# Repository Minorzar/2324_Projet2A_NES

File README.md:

# FPGA NES - Student Project

This repository contains a recreation of the NES console (EU edition) in **VHDL language**. We used **Quartus** for all of the VHDL part of the project, and uploaded it on the **DE1-SoC board RevC (Cyclone V)**. 
Also, this project have a PCB designed for the FPGA board to be able to connect with the NES cartridge. (Realised under KiCad 7.0+). 

## Notes : 6502 CPU

A part of this project replicates the 6502 CPU in VHDL language. Feel free to use whatever part of the code for your projects. 
> **Note:** We aim to create a repository which contains only the 6502. A link will be added to this repository when it will be done.

## Repository Structure

- **Hardware** : The PCB for the Cartridge adaptator. Use the V5 currently. Only the latest version of it will be available later. You still need to buy the cartridge lector himself online, because the PCB only replicate a part of the PCB of the NES.
- **Software** :  Contains the architecture in VHDL of the NES. Details later on the readme.
- **Datasheet** : Contains all the datasheets used for the project. All other data comes from the [NESdev wiki](https://www.nesdev.org/wiki/Nesdev_Wiki).

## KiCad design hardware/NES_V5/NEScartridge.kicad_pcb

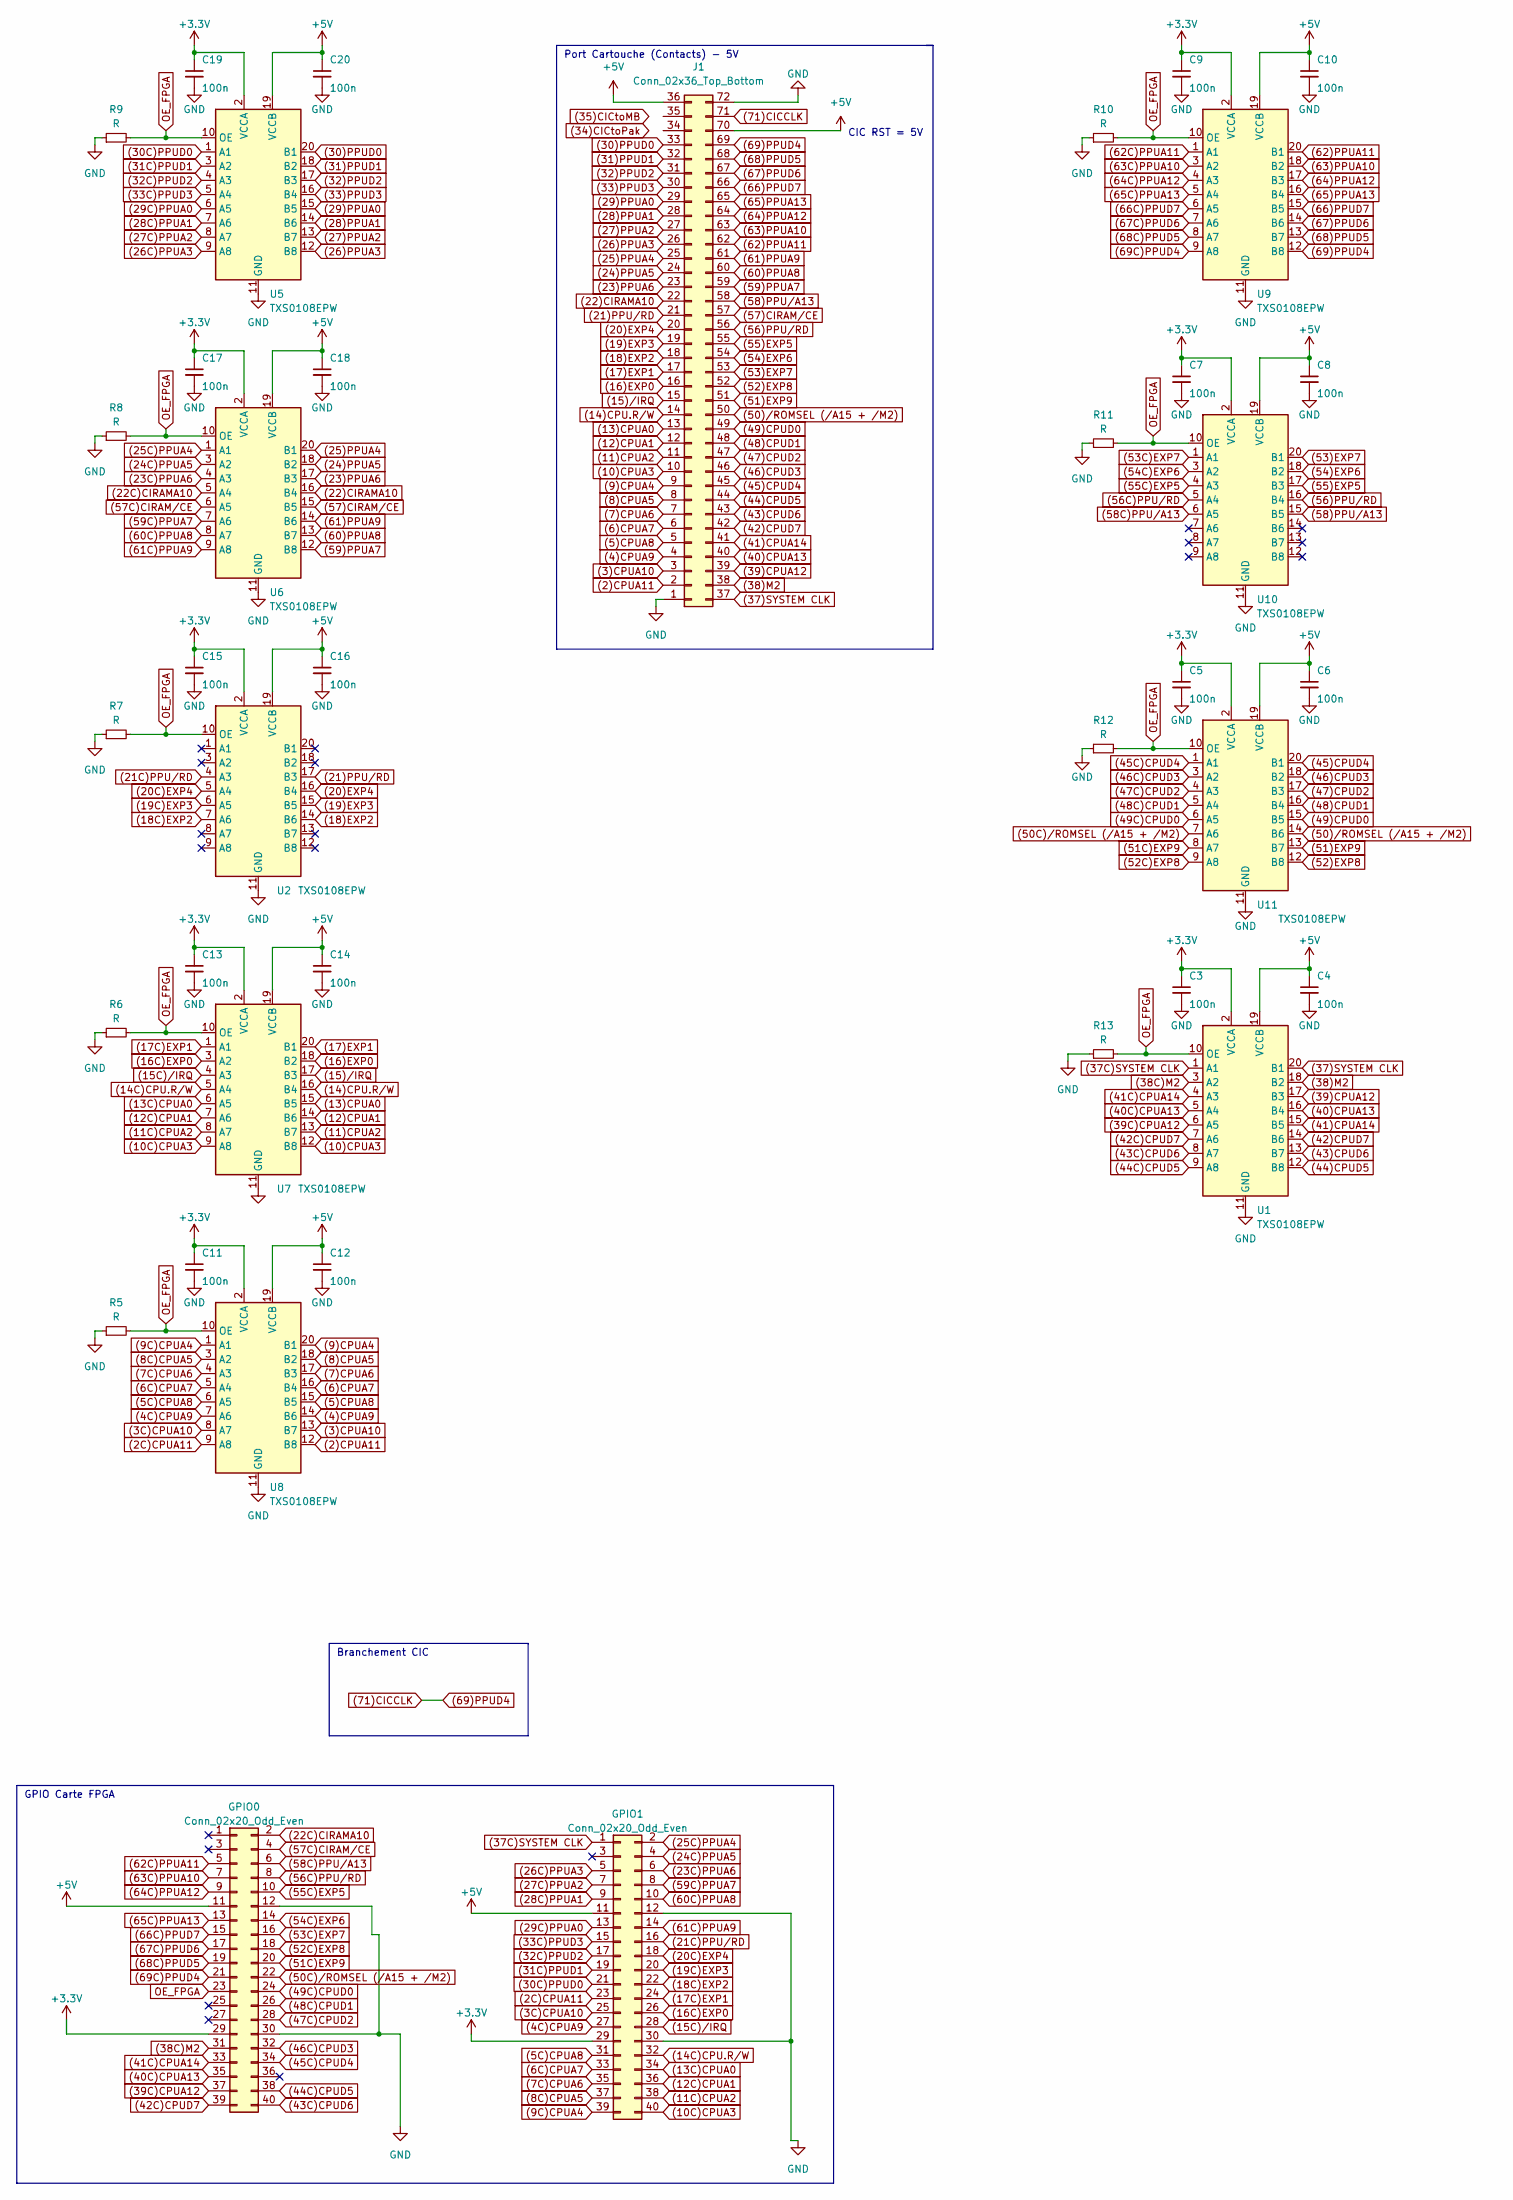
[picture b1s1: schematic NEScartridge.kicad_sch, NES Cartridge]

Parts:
C3, C4, C5, C6, C7, C8, C9, C10, C11, C12, C13, C14, C15, C16, C17, C18, C19, C20: 100n; C_0402_1005Metric
GPIO0, GPIO1: Conn_02x20_Odd_Even; PinHeader_2x20_P2.54mm_Vertical
J1: Conn_02x36_Top_Bottom; NES_Edge_Connector
R5, R6, R7, R8, R9, R10, R11, R12, R13: R; R_0402_1005Metric_Pad0.72x0.64mm_HandSolder
U1, U2, U5, U6, U7, U8, U9, U10, U11: TXS0108EPW; TSSOP-20_4.4x6.5mm_P0.65mm

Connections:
(2)CPUA11: J1.2, U8.12 (B8)
(2C)CPUA11: GPIO1.23, U8.9 (A8)
(3)CPUA10: J1.3, U8.13 (B7)
(3C)CPUA10: GPIO1.25, U8.8 (A7)
(4)CPUA9: J1.4, U8.14 (B6)
(4C)CPUA9: GPIO1.27, U8.7 (A6)
(5)CPUA8: J1.5, U8.15 (B5)
(5C)CPUA8: GPIO1.31, U8.6 (A5)
(6)CPUA7: J1.6, U8.16 (B4)
(6C)CPUA7: GPIO1.33, U8.5 (A4)
(7)CPUA6: J1.7, U8.17 (B3)
(7C)CPUA6: GPIO1.35, U8.4 (A3)
(8)CPUA5: J1.8, U8.18 (B2)
(8C)CPUA5: GPIO1.37, U8.3 (A2)
(9)CPUA4: J1.9, U8.20 (B1)
(9C)CPUA4: GPIO1.39, U8.1 (A1)
(10)CPUA3: J1.10, U7.12 (B8)
(10C)CPUA3: GPIO1.40, U7.9 (A8)
(11)CPUA2: J1.11, U7.13 (B7)
(11C)CPUA2: GPIO1.38, U7.8 (A7)
(12)CPUA1: J1.12, U7.14 (B6)
(12C)CPUA1: GPIO1.36, U7.7 (A6)
(13)CPUA0: J1.13, U7.15 (B5)
(13C)CPUA0: GPIO1.34, U7.6 (A5)
(14)CPU.R/W: J1.14, U7.16 (B4)
(14C)CPU.R/W: GPIO1.32, U7.5 (A4)
(15)/IRQ: J1.15, U7.17 (B3)
(15C)/IRQ: GPIO1.28, U7.4 (A3)
(16)EXP0: J1.16, U7.18 (B2)
(16C)EXP0: GPIO1.26, U7.3 (A2)
(17)EXP1: J1.17, U7.20 (B1)
(17C)EXP1: GPIO1.24, U7.1 (A1)
(18)EXP2: J1.18, U2.14 (B6)
(18C)EXP2: GPIO1.22, U2.7 (A6)
(19)EXP3: J1.19, U2.15 (B5)
(19C)EXP3: GPIO1.20, U2.6 (A5)
(20)EXP4: J1.20, U2.16 (B4)
(20C)EXP4: GPIO1.18, U2.5 (A4)
(21)PPU/RD: J1.21, U2.17 (B3)
(21C)PPU/RD: GPIO1.16, U2.4 (A3)
(22)CIRAMA10: J1.22, U6.16 (B4)
(22C)CIRAMA10: GPIO0.2, U6.5 (A4)
(23)PPUA6: J1.23, U6.17 (B3)
(23C)PPUA6: GPIO1.6, U6.4 (A3)
(24)PPUA5: J1.24, U6.18 (B2)
(24C)PPUA5: GPIO1.4, U6.3 (A2)
(25)PPUA4: J1.25, U6.20 (B1)
(25C)PPUA4: GPIO1.2, U6.1 (A1)
(26)PPUA3: J1.26, U5.12 (B8)
(26C)PPUA3: GPIO1.5, U5.9 (A8)
(27)PPUA2: J1.27, U5.13 (B7)
(27C)PPUA2: GPIO1.7, U5.8 (A7)
(28)PPUA1: J1.28, U5.14 (B6)
(28C)PPUA1: GPIO1.9, U5.7 (A6)
(29)PPUA0: J1.29, U5.15 (B5)
(29C)PPUA0: GPIO1.13, U5.6 (A5)
(30)PPUD0: J1.33, U5.20 (B1)
(30C)PPUD0: GPIO1.21, U5.1 (A1)
(31)PPUD1: J1.32, U5.18 (B2)
(31C)PPUD1: GPIO1.19, U5.3 (A2)
(32)PPUD2: J1.31, U5.17 (B3)
(32C)PPUD2: GPIO1.17, U5.4 (A3)
(33)PPUD3: J1.30, U5.16 (B4)
(33C)PPUD3: GPIO1.15, U5.5 (A4)
(34)CICtoPak: J1.34
(35)CICtoMB: J1.35
(37)SYSTEM CLK: J1.37, U1.20 (B1)
(37C)SYSTEM CLK: GPIO1.1, U1.1 (A1)
(38)M2: J1.38, U1.18 (B2)
(38C)M2: GPIO0.31, U1.3 (A2)
(39)CPUA12: J1.39, U1.17 (B3)
(39C)CPUA12: GPIO0.37, U1.6 (A5)
(40)CPUA13: J1.40, U1.16 (B4)
(40C)CPUA13: GPIO0.35, U1.5 (A4)
(41)CPUA14: J1.41, U1.15 (B5)
(41C)CPUA14: GPIO0.33, U1.4 (A3)
(42)CPUD7: J1.42, U1.14 (B6)
(42C)CPUD7: GPIO0.39, U1.7 (A6)
(43)CPUD6: J1.43, U1.13 (B7)
(43C)CPUD6: GPIO0.40, U1.8 (A7)
(44)CPUD5: J1.44, U1.12 (B8)
(44C)CPUD5: GPIO0.38, U1.9 (A8)
(45)CPUD4: J1.45, U11.20 (B1)
(45C)CPUD4: GPIO0.34, U11.1 (A1)
(46)CPUD3: J1.46, U11.18 (B2)
(46C)CPUD3: GPIO0.32, U11.3 (A2)
(47)CPUD2: J1.47, U11.17 (B3)
(47C)CPUD2: GPIO0.28, U11.4 (A3)
(48)CPUD1: J1.48, U11.16 (B4)
(48C)CPUD1: GPIO0.26, U11.5 (A4)
(49)CPUD0: J1.49, U11.15 (B5)
(49C)CPUD0: GPIO0.24, U11.6 (A5)
(50)/ROMSEL (/A15 + /M2): J1.50, U11.14 (B6)
(50C)/ROMSEL (/A15 + /M2): GPIO0.22, U11.7 (A6)
(51)EXP9: J1.51, U11.13 (B7)
(51C)EXP9: GPIO0.20, U11.8 (A7)
(52)EXP8: J1.52, U11.12 (B8)
(52C)EXP8: GPIO0.18, U11.9 (A8)
(53)EXP7: J1.53, U10.20 (B1)
(53C)EXP7: GPIO0.16, U10.1 (A1)
(54)EXP6: J1.54, U10.18 (B2)
(54C)EXP6: GPIO0.14, U10.3 (A2)
(55)EXP5: J1.55, U10.17 (B3)
(55C)EXP5: GPIO0.10, U10.4 (A3)
(56)PPU/RD: J1.56, U10.16 (B4)
(56C)PPU/RD: GPIO0.8, U10.5 (A4)
(57)CIRAM/CE: J1.57, U6.15 (B5)
(57C)CIRAM/CE: GPIO0.4, U6.6 (A5)
(58)PPU/A13: J1.58, U10.15 (B5)
(58C)PPU/A13: GPIO0.6, U10.6 (A5)
(59)PPUA7: J1.59, U6.12 (B8)
(59C)PPUA7: GPIO1.8, U6.7 (A6)
(60)PPUA8: J1.60, U6.13 (B7)
(60C)PPUA8: GPIO1.10, U6.8 (A7)
(61)PPUA9: J1.61, U6.14 (B6)
(61C)PPUA9: GPIO1.14, U6.9 (A8)
(62)PPUA11: J1.62, U9.20 (B1)
(62C)PPUA11: GPIO0.5, U9.1 (A1)
(63)PPUA10: J1.63, U9.18 (B2)
(63C)PPUA10: GPIO0.7, U9.3 (A2)
(64)PPUA12: J1.64, U9.17 (B3)
(64C)PPUA12: GPIO0.9, U9.4 (A3)
(65)PPUA13: J1.65, U9.16 (B4)
(65C)PPUA13: GPIO0.13, U9.5 (A4)
(66)PPUD7: J1.66, U9.15 (B5)
(66C)PPUD7: GPIO0.15, U9.6 (A5)
(67)PPUD6: J1.67, U9.14 (B6)
(67C)PPUD6: GPIO0.17, U9.7 (A6)
(68)PPUD5: J1.68, U9.13 (B7)
(68C)PPUD5: GPIO0.19, U9.8 (A7)
(69)PPUD4: J1.69, J1.71, U9.12 (B8)
(69C)PPUD4: GPIO0.21, U9.9 (A8)
+3.3V: C3.1, C5.1, C7.1, C9.1, C11.1, C13.1, C15.1, C17.1, C19.1, GPIO0.29, GPIO1.29, U1.2 (VCCA), U2.2 (VCCA), U5.2 (VCCA), U6.2 (VCCA), U7.2 (VCCA), U8.2 (VCCA), U9.2 (VCCA), U10.2 (VCCA), U11.2 (VCCA)
+5V: C4.1, C6.1, C8.1, C10.1, C12.1, C14.1, C16.1, C18.1, C20.1, GPIO0.11, GPIO1.11, J1.36, J1.70, U1.19 (VCCB), U2.19 (VCCB), U5.19 (VCCB), U6.19 (VCCB), U7.19 (VCCB), U8.19 (VCCB), U9.19 (VCCB), U10.19 (VCCB), U11.19 (VCCB)
GND: C3.2, C4.2, C5.2, C6.2, C7.2, C8.2, C9.2, C10.2, C11.2, C12.2, C13.2, C14.2, C15.2, C16.2, C17.2, C18.2, C19.2, C20.2, GPIO0.12, GPIO0.30, GPIO1.12, GPIO1.30, J1.1, J1.72, R5.1, R6.1, R7.1, R8.1, R9.1, R10.1, R11.1, R12.1, R13.1, U1.11 (GND), U2.11 (GND), U5.11 (GND), U6.11 (GND), U7.11 (GND), U8.11 (GND), U9.11 (GND), U10.11 (GND), U11.11 (GND)
OE_FPGA: GPIO0.23, R5.2, R6.2, R7.2, R8.2, R9.2, R10.2, R11.2, R12.2, R13.2, U1.10 (OE), U2.10 (OE), U5.10 (OE), U6.10 (OE), U7.10 (OE), U8.10 (OE), U9.10 (OE), U10.10 (OE), U11.10 (OE)

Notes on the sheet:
Port Cartouche (Contacts) - 5V
CIC RST = 5V
GPIO Carte FPGA
Branchement CIC

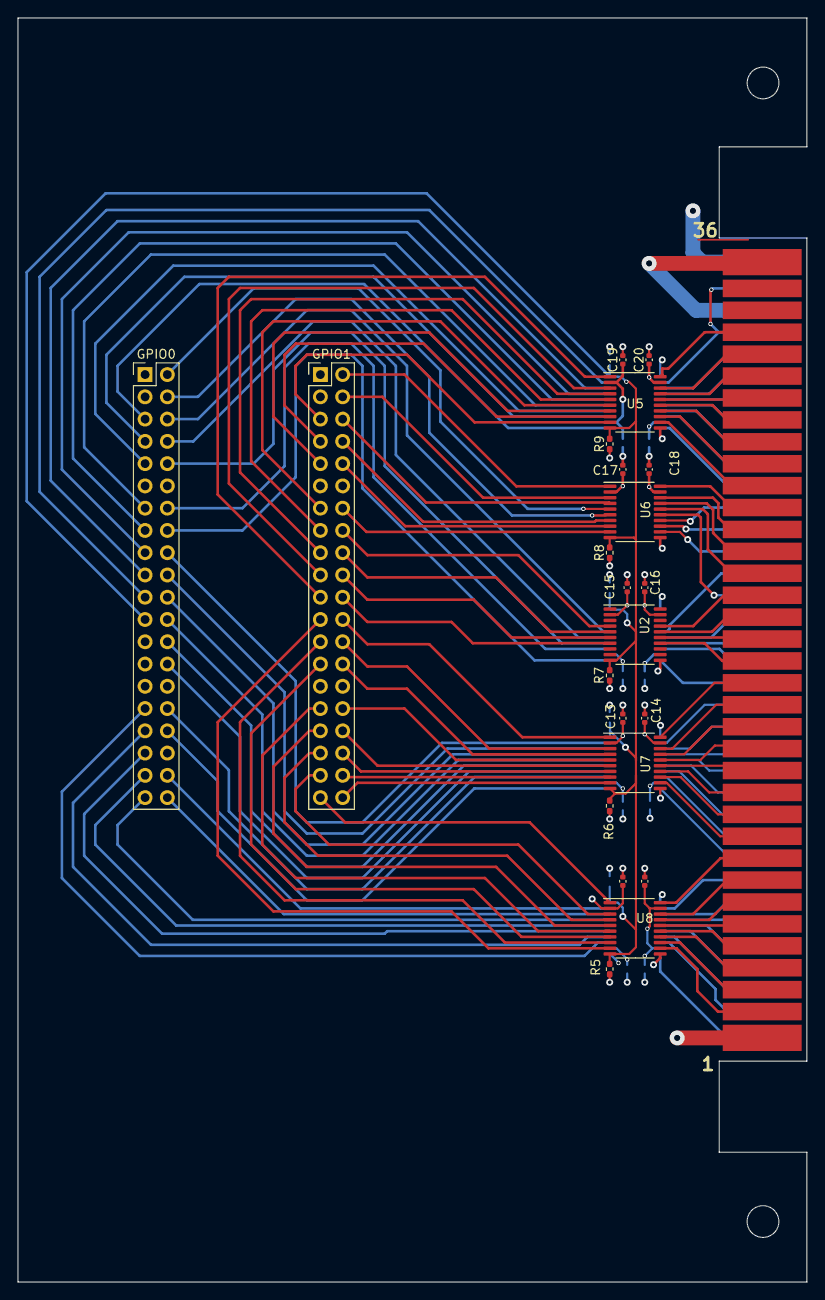
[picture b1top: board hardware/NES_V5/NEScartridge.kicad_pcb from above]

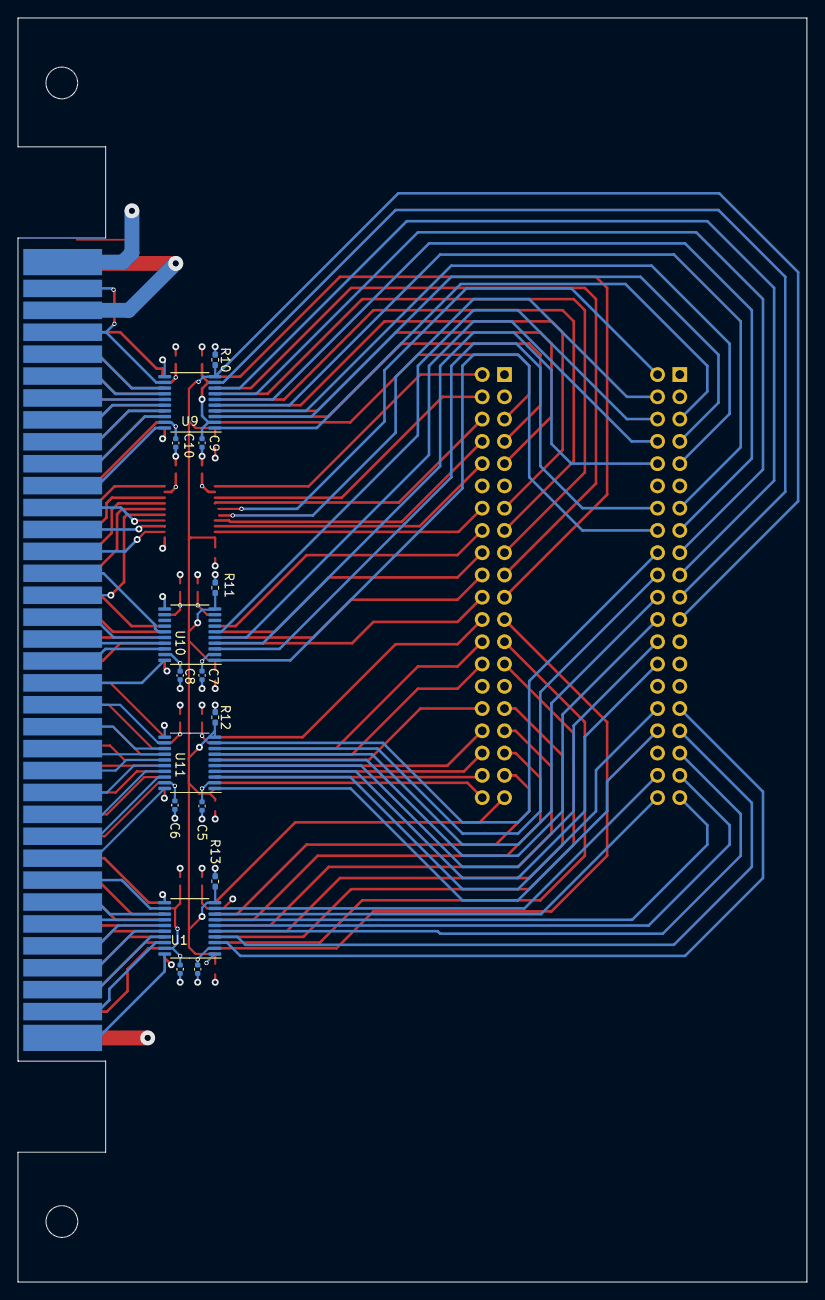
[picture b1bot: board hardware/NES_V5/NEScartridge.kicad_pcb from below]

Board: 4 copper layers, 90.0 x 144.2 mm, 39 parts (16 on the bottom side), 134 nets.

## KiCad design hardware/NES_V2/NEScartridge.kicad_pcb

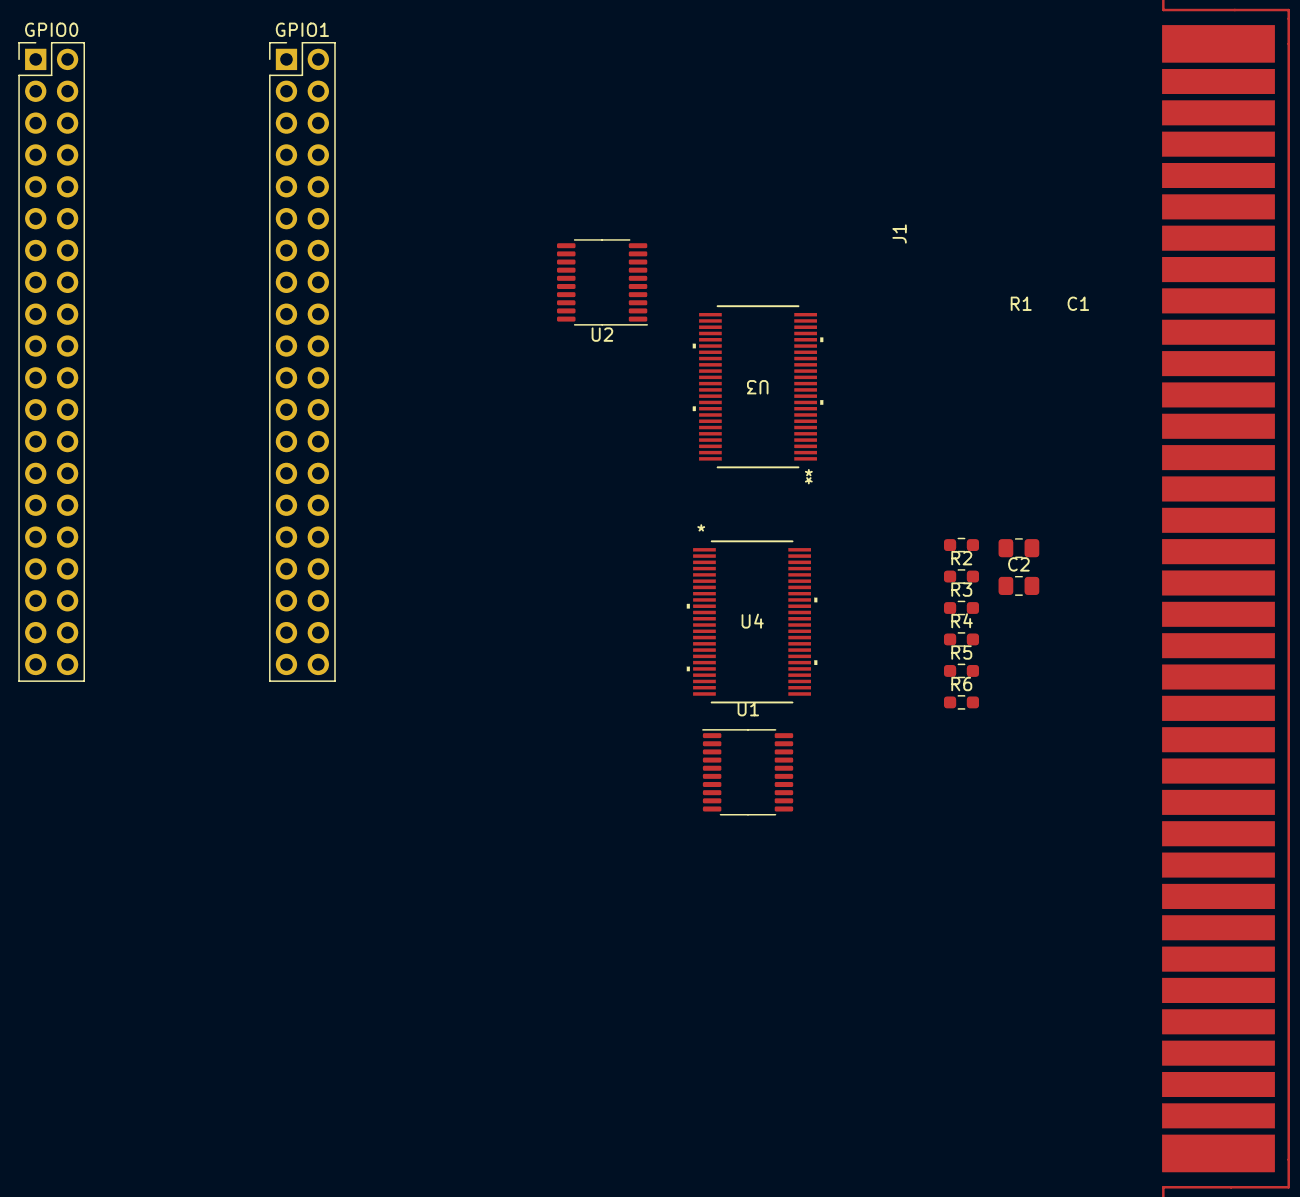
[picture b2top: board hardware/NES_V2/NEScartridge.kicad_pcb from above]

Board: 2 copper layers, 15 parts (0 on the bottom side), 98 nets, no tracks yet.

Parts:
C1, C2: 0.1 uF; C_0805_2012Metric_Pad1.18x1.45mm_HandSolder
GPIO0, GPIO1: Conn_02x20_Odd_Even; PinHeader_2x20_P2.54mm_Vertical
J1: Conn_02x36_Top_Bottom; NES_Edge_Connector
R1, R2: 10k; R_0603_1608Metric_Pad0.98x0.95mm_HandSolder
R3, R4, R5, R6: R; R_0603_1608Metric_Pad0.98x0.95mm_HandSolder
U1, U2: TXS0108EPW; TSSOP-20_4.4x6.5mm_P0.65mm
U3, U4: 74ALVC164245DGG; SOT362-1_NXP-M

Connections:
(2)CPUA11: J1.2, U3.17 (2B3)
(2C)CPUA11: GPIO0.27, U3.32 (2A3)
(3)CPUA10: J1.3, U3.16 (2B2)
(3C)CPUA10: GPIO0.25, U3.33 (2A2)
(4)CPUA9: J1.4, U3.14 (2B1)
(4C)CPUA9: GPIO0.23, U3.35 (2A1)
(5)CPUA8: J1.5, U3.13 (2B0)
(5C)CPUA8: GPIO0.21, U3.36 (2A0)
(6)CPUA7: J1.6, U3.12 (1B7)
(6C)CPUA7: GPIO0.19, U3.37 (1A7)
(7)CPUA6: J1.7, U3.11 (1B6)
(7C)CPUA6: GPIO0.17, U3.38 (1A6)
(8)CPUA5: J1.8, U3.9 (1B5)
(8C)CPUA5: GPIO0.15, U3.40 (1A5)
(9)CPUA4: J1.9, U3.8 (1B4)
(9C)CPUA4: GPIO0.9, U3.41 (1A4)
(10)CPUA3: J1.10, U3.6 (1B3)
(10C)CPUA3: GPIO0.7, U3.43 (1A3)
(11)CPUA2: J1.11, U3.5 (1B2)
(11C)CPUA2: GPIO0.5, U3.44 (1A2)
(12)CPUA1: J1.12, U3.3 (1B1)
(12C)CPUA1: GPIO0.3, U3.46 (1A1)
(13)CPUA0: J1.13, U3.2 (1B0)
(13C)CPUA0: GPIO0.13, U3.47 (1A0)
(23)PPUA6: J1.23, U4.11 (1B6)
(23C)PPUA6: GPIO1.16, U4.38 (1A6)
(24)PPUA5: J1.24, U4.9 (1B5)
(24C)PPUA5: GPIO1.14, U4.40 (1A5)
(25)PPUA4: J1.25, U4.8 (1B4)
(25C)PPUA4: GPIO1.10, U4.41 (1A4)
(26)PPUA3: J1.26, U4.6 (1B3)
(26C)PPUA3: GPIO1.8, U4.43 (1A3)
(27)PPUA2: J1.27, U4.5 (1B2)
(27C)PPUA2: GPIO1.6, U4.44 (1A2)
(28)PPUA1: J1.28, U4.3 (1B1)
(28C)PPUA1: GPIO1.4, U4.46 (1A1)
(29)PPUA0: J1.29, U4.2 (1B0)
(29C)PPUA0: GPIO1.2, U4.47 (1A0)
(30)PPUD0: J1.33, U1.20 (B1)
(30C)PPUD0: GPIO1.9, U1.1 (A1)
(31)PPUD1: J1.32, U1.18 (B2)
(31C)PPUD1: GPIO1.13, U1.3 (A2)
(32)PPUD2: J1.31, U1.17 (B3)
(32C)PPUD2: GPIO1.15, U1.4 (A3)
(33)PPUD3: J1.30, U1.16 (B4)
(33C)PPUD3: GPIO1.17, U1.5 (A4)
(39C)CPUA12: GPIO0.31, U3.19 (2B4), U3.30 (2A4)
(40C)CPUA13: GPIO0.33, U3.20 (2B5), U3.29 (2A5)
(41C)CPUA14: GPIO0.35, U3.22 (2B6), U3.27 (2A6)
(42)CPUD7: J1.42, U2.12 (B8)
(42C)CPUD7: GPIO0.18, U2.9 (A8)
(43)CPUD6: J1.43, U2.13 (B7)
(43C)CPUD6: GPIO0.16, U2.8 (A7)
(44)CPUD5: J1.44, U2.14 (B6)
(44C)CPUD5: GPIO0.14, U2.7 (A6)
(45)CPUD4: J1.45, U2.15 (B5)
(45C)CPUD4: GPIO0.10, U2.6 (A5)
(46)CPUD3: J1.46, U2.16 (B4)
(46C)CPUD3: GPIO0.8, U2.5 (A4)
(47)CPUD2: J1.47, U2.17 (B3)
(47C)CPUD2: GPIO0.6, U2.4 (A3)
(48)CPUD1: J1.48, U2.18 (B2)
(48C)CPUD1: GPIO0.4, U2.3 (A2)
(49)CPUD0: J1.49, U2.20 (B1)
(49C)CPUD0: GPIO0.2, U2.1 (A1)
(59)PPUA7: J1.59, U4.12 (1B7)
(59C)PPUA7: GPIO1.18, U4.37 (1A7)
(60)PPUA8: J1.60, U4.13 (2B0)
(60C)PPUA8: GPIO1.20, U4.36 (2A0)
(61)PPUA9: J1.61, U4.14 (2B1)
(61C)PPUA9: GPIO1.22, U4.35 (2A1)
(62)PPUA11: J1.62, U4.16 (2B2)
(62C)PPUA11: GPIO1.24, U4.33 (2A2)
(63)PPUA10: J1.63, U4.17 (2B3)
(63C)PPUA10: GPIO1.26, U4.32 (2A3)
(64)PPUA12: J1.64, U4.19 (2B4)
(64C)PPUA12: GPIO1.28, U4.30 (2A4)
(65)PPUA13: J1.65, U4.20 (2B5)
(65C)PPUA13: GPIO1.32, U4.29 (2A5)
(66)PPUD7: J1.66, U1.12 (B8)
(66C)PPUD7: GPIO1.25, U1.9 (A8)
(67)PPUD6: J1.67, U1.13 (B7)
(67C)PPUD6: GPIO1.23, U1.8 (A7)
(68)PPUD5: J1.68, U1.14 (B6)
(68C)PPUD5: GPIO1.21, U1.7 (A6)
(69)PPUD4: J1.69, U1.15 (B5)
(69C)PPUD4: GPIO1.19, U1.6 (A5)
GND: C1.2, C2.2, GPIO0.12, GPIO0.30, GPIO1.12, GPIO1.30, J1.1, J1.72, R1.2, R2.2, U1.11 (GND), U2.11 (GND), U4.4 (GND), U4.10 (GND), U4.15 (GND), U4.21 (GND)
GND.U3: U3.4 (GND), U3.10 (GND), U3.15 (GND), U3.21 (GND), U3.28 (GND), U3.34 (GND), U3.39 (GND), U3.45 (GND)
GND.U4: U4.28 (GND), U4.34 (GND), U4.39 (GND), U4.45 (GND)
unnamed: R1.1, U1.10 (OE)
unnamed: R2.1, U2.10 (OE)
unnamed: R3.1, U3.48 (1OE*)
unnamed: R4.2, U3.25 (2OE*)
unnamed: R5.1, U4.48 (1OE*)
unnamed: R6.2, U4.25 (2OE*)
VcA: C1.1, GPIO0.29, GPIO1.29, R3.2, R4.1, R5.2, R6.1, U1.2 (VCCA), U2.2 (VCCA), U3.31 (VCC(A)), U3.42 (VCC(A)), U4.31 (VCC(A)), U4.42 (VCC(A))
VcB: C2.1, GPIO0.11, GPIO1.11, U1.19 (VCCB), U2.19 (VCCB), U3.7 (VCC(B)), U3.18 (VCC(B)), U4.7 (VCC(B)), U4.18 (VCC(B))

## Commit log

2023-10-03 Added Nintendo Entertainment System Documentation
2023-10-03 Add the basic architecture of the git repository
2023-10-03 Add the blank FPGA project
2023-10-03 Added Everynes NES Hardware Specifications and Nintendo Entertainment System (NES) Architecture (Link)
2023-10-03 Work once again on the test FPGA file, just to make everything works
2023-10-17 Update from last time (forgot to commit it)
2023-10-17 big datasheet
2023-10-17 Added 6502-Block-Diagram.pdf - Updated README_datasheet
2023-10-17 Added w65c02s.pdf (W65C02S 8–bit Microprocessor Datasheet)
2023-10-17 Add the VGA file
2023-10-17 my part
2023-10-24 New version: change of code + VGA file
    Code changes to make it cleaner. VGA file has been added and soon will be work on
2023-10-24 Added schematic of the NES cartridge adaptator
2023-10-24 Added datasheets
2023-10-24 Test commit: see if branch is working
2023-10-24 branch is working
2023-10-24 gitignore
2023-10-24 fpga work
2023-10-24 Update project structure: Proc_Quartus created
2023-10-24 Test commit: branch has an issue, try to fix it
2023-10-24 issue fixed
2023-10-24 Updated datasheets
2023-11-07 update of all vhdl for the ram
2023-11-07 ram datasheet
2023-11-07 Datasheet
2023-11-14 Update of the RAM
    * update of all vhdl for the ram
    * ram datasheet
    ---------
2023-11-14 CPU module + execution submodules
    Added all the VHDL modules I had been working on since the beginning. Includes an incomplete draft of the CPU module and most execution submodules.
2023-11-14 FINISHED
2023-11-14 Added README_decode
2023-11-14 Update VGA: VGA_Sync working
2023-11-15 Issue #10 - Add testbench + correction of code
2023-11-17 Issue #10 - +comm +ctrl, res=>1280x1024
2023-11-27 Add of V2 and V3 of the cartdrige adadpter
2023-11-27 Update on the V3 of the cartridge
2023-11-27 Update on the V3 of the cartridge - PCB
2023-11-28 CPU Decode.vhd - Added predecode, instruction_register, timing_generation_logic
2023-11-28 Clean Up
2023-11-28 Issue #14 - Added V4 of the cartridge
2023-11-28 issue #10 - Code cleared and corrected, still some issues
2023-12-05 ROM half down, waiting to see what is in the ROM
2023-12-05 Backup
2023-12-05 #14 Added GND, 5V and 3.3V layout and fixed some bugs
2023-12-05 fixed errors and improved the synthetization of the execution modules
2023-12-05 #10 - Still not working, but on the way
2023-12-05 FOUND ALL THE 6502 with TRANSISTOR
2023-12-12 Predecode: Fixed predecode & Added testbench
2023-12-12 Corrected DRC errors/warning on V5
2023-12-12 Predecode: Update predecode (WIP)
2023-12-19 Backup #12
2023-12-19 #12 Predecode: Overhauled predecode_register, predecode_logic
2024-01-16 Issue #10 - It's FINALLY working, I don't know why it wasn't the case before and I don't know why it works now but it works
2024-01-16 Refractor and reorganise folders
2024-01-16 Resolved merging issue
2024-01-16 #12 Updated predecode_register, predecode_logic, instruction_register, timing_generation logic
2024-01-19 Added predecode_register, predecode_logic, instruction_register, timing_generation_logic - Implemented package_opcode_determination
2024-01-20 #12 Implemented package_addressing_mode_determination
2024-01-22 #12 Implemented package_cycles_required (WIP) & Bug Fixes
2024-01-22 #12 Bug Fixes
2024-01-22 #12 Improved syntaxes
2024-01-23 data about PPU
2024-01-23 signal in PPU down
2024-01-23 accurate datasheet for Famcom pcb
2024-01-23 #12 Updated package_cycles_required (Implied, JSR, Read-Modify-Write, Indirect) & Updated Null cases
2024-01-23 updated the CPU execution submodules and the CPU module, ALU not functional yet
2024-01-23 add on ppu
2024-01-23 Sorted folders
2024-01-23 Upgrades on the PCBs
2024-01-23 set up of the inout + register
2024-01-23 Changed the README file
2024-01-23 CPU_xy_register testbench done
2024-01-23 chagement in the makefile PPU
2024-01-23 #12 Reworked : predecode_register, predecode_logic, instruction_register, decode_rom
2024-01-23 CPU_clock_generator testbench done
2024-01-23 fixed partially the clock generator and a few things about the CPU module, first functional draft of ALU
2024-01-25 Fixed previous commit
2024-01-25 CPU_address_bus_register testbench done
2024-01-26 avencement in Datasheet PPU aka Readme PPU
2024-01-28 #12 Refactored & Added comments: predecode_register, instruction_register, decode_rom
2024-01-28 #12 Updated predecode_logic
2024-01-29 #12 Fixed typos
2024-01-30 #12 Added timing_generator_logic (WIP)
2024-01-30 finished and modified CPU execution modules, further testing needed
2024-01-30 #12 Added decode_tb.vhd
2024-01-30 #12 Fixed refactoring typos
2024-01-30 #12 Updated decode_tb stimulus process (WIP)
2024-01-30 more data about PPU
2024-01-30 Modify gitignore to handle db, incremental_db, simulation and output_files from Quartus projects
2024-01-30 Forgot to update the gitignore file
2024-01-30 Merging
2024-01-30 start of tb
2024-01-30 extand datasheet PPU
2024-01-30 #12 Added template_latch.vhd
2024-01-30 #12 Rewrote predecode_register.vhd
2024-01-30 #12 Rewrote instruction_register.vhd
2024-01-30 Added the APU project + created the sequencer of the triangle
2024-01-30 Remove useless backups from kicad project
2024-01-30 #12 Rewrote predecode_logic & Fixed instruction_register
2024-01-30 #12 Updated naming convention (WIP)
2024-02-01 #12 Completed Refactoring & Added Placeholders (interrupt_and_reset_control, ready_control)
2024-02-05 added the array of linear counter of the length counter
2024-02-06 #12 Refactor
2024-02-06 #12 Added predecode_register_tb
2024-02-06 Added the linear counter register and linear counter
2024-02-06 #12 Refactored project & Completed tb_predecode_logic
2024-02-06 #12 Fixed predecode_logic syntax errors
2024-02-06 #12 Added tb_predecode_logic (WIP)
2024-02-06 Correction of the AC testbench + ALU testbench, seems to have an error in the sum of the ALU
2024-02-07 CPU_ALU corrected
2024-02-07 a_input_register testbench done
2024-02-09 stack_pointer testbench done, rework simulation profile
2024-02-23 #12 tb_predecode_logic (Backup)
2024-02-23 #12 Implemented predecode_logic, tb_predecode_logic | Updated top level
2024-02-24 #12 Fixed predecode_logic & tb_predecode_logic
2024-02-25 #12 Added tb_instruction_register
2024-02-25 #12 Updated decode.vhd
2024-02-25 #12 Fixed decode & instruction_register bugs
2024-02-26 random control logic odule almost finished
2024-02-26 #12 Updated tb_instruction_register
2024-02-26 #12 Fixed timing_generator_logic
2024-02-26 reset down
2024-02-26 #12 Implemented timing_generator_logic
2024-02-26 #12 Implemented tb_timing_generator_logic
2024-02-26 #12 Implemented decode_rom & Updated decode
2024-02-27 Vacancy update
2024-02-27 random_control_logic almost functional
2024-02-27 Updated README_datasheet, README_decode
2024-02-27 Triangle Module Update
2024-02-27 testbench of adder hold register done
2024-02-27 #12 tb_timing_generation_logic (WIP) & Fixed predecode_logic & timing_generation logic active signal & Fixed decode sensitivity list
2024-02-27 go on CODEC
2024-03-01 #12 tb_timing_generation_logic - Backup
2024-03-04 #12 Updated tb_timing_generation_logic
2024-03-05 commit of last week, random control logic is finally complete but needs testing
2024-03-05 #12 tb_timing_generation_logic & timing_generation_logic backups
2024-03-05 #12 Timing Generation Logic: Bug Fixes / Testbench / Temporary Truth Table
2024-03-05 compt finish
2024-03-05 stack down
2024-03-12 CPU_data_output_register_buffer testbench done
2024-03-12 modify gitignore, now ignoring .bak files
2024-03-12 clear git from .bak files
2024-03-12 #12 Added tb_decode_rom (WIP)
2024-03-12 int and reset control almost finished
2024-03-12 #12 Fixed tb_decode_rom (WIP)
2024-03-12 Added frame counter and env.generator
2024-03-12 remove bak file (forced to commit to resolve merge issue)
2024-03-12 Update of main, resolve some issues
2024-03-12 Overall debug
2024-03-12 #12 Added readme_decode_rom
2024-03-12 #12 Updated tb_decode_rom
2024-03-12 test on quartus
2024-03-12 I suppose b_input_register_tb is working (undefined signal at first rising edge, maybe a timing issue ?)
2024-03-13 #12 decode_rom bugs to be fixed
2024-03-14 #12 Fixed decode_rom (WIP)
2024-03-15 #12 Fixed tb_decode_rom
2024-03-16 #12 Updated tb_predecode_register
2024-03-17 #12 Updated tb_predecode_logic
2024-03-18 #12 Refactored tb_decode_rom
2024-03-18 #12 Fixed tb_decode_rom & Updated readme_decode_rom
2024-03-18 #12 Refactored testbenches
2024-03-18 #12 Updated Readme & Clean Up
2024-03-18 #12 Fixed tb_predecode_logic
2024-03-19 all modules finished, modifications of 2 of them are necessary
2024-03-19 #12 Updated README_timing_generation_logic equations & Updated comments
2024-03-19 #12 Updated README_timing_generation_logic truth table
2024-03-19 new compter
2024-03-19 Corrected linear counter and added clk_divider
2024-03-19 new better serialiser
2024-03-21 #12 Updaded README_timing_generation_logic (Added stimulus process)
2024-03-22 #12 Completed tb_timing_generation_logic
2024-03-26 debugging
2024-03-26 files tested and fixed
2024-03-26 #12 Added more test cases to tb_timing_generation_logic & Updated README_timing_generation_logic
2024-03-26 #12 Updated README_decode_rom
2024-03-26 #12 Updated decode top-level module
2024-03-26 Added Shift Register, Timer, Clk_divider and corrected bugs
2024-03-26 #12 Updated README_decode & datasheets folder
2024-03-26 fixed the assembly module and some signal naming issues
2024-03-26 serialisor finish
2024-03-26 Added APU_noise and APU_sweep
2024-03-26 clock_regulator ok
2024-03-26 new RAM and base of APU register
2024-03-26 all modules are finished and assembled. Only needs to be debugged now
2024-03-27 fixed various issues with buffers and unused signals
2024-03-27 new APU_register with high impedence
2024-03-27 it's compile
2024-03-27 Corrected bugs
2024-03-27 APU register works
2024-03-27 finaly the true ram is come
2024-03-27 ok, new ram
2024-03-27 ram buffed
2024-03-27 rework register APU for std_logic
2024-03-28 Update tb for interrupt, it's not yet functional
2024-03-28 fixed a small issue while merging
2024-03-29 apu register in APU
2024-03-29 fixe my files
2024-03-29 added Esteban's 74LS139 files
2024-03-29 Correction of bugs
2024-03-29 fixed input in CPU_test_vontrol
2024-03-29 fixed CPU_test_control again
2024-03-29 Add an automatic testbench writting programm, will be upgraded soon, work for CPU_test_control
2024-03-30 completely reworked the execution modules to avoid using tri-state logic
2024-03-30 Correction of bugs, added APU_noise
2024-03-30 Corrected Bugs. Push for further merge
2024-03-30 new RAM_i_o
2024-04-02 various changes and fixes, spcified the initial states of many signals
